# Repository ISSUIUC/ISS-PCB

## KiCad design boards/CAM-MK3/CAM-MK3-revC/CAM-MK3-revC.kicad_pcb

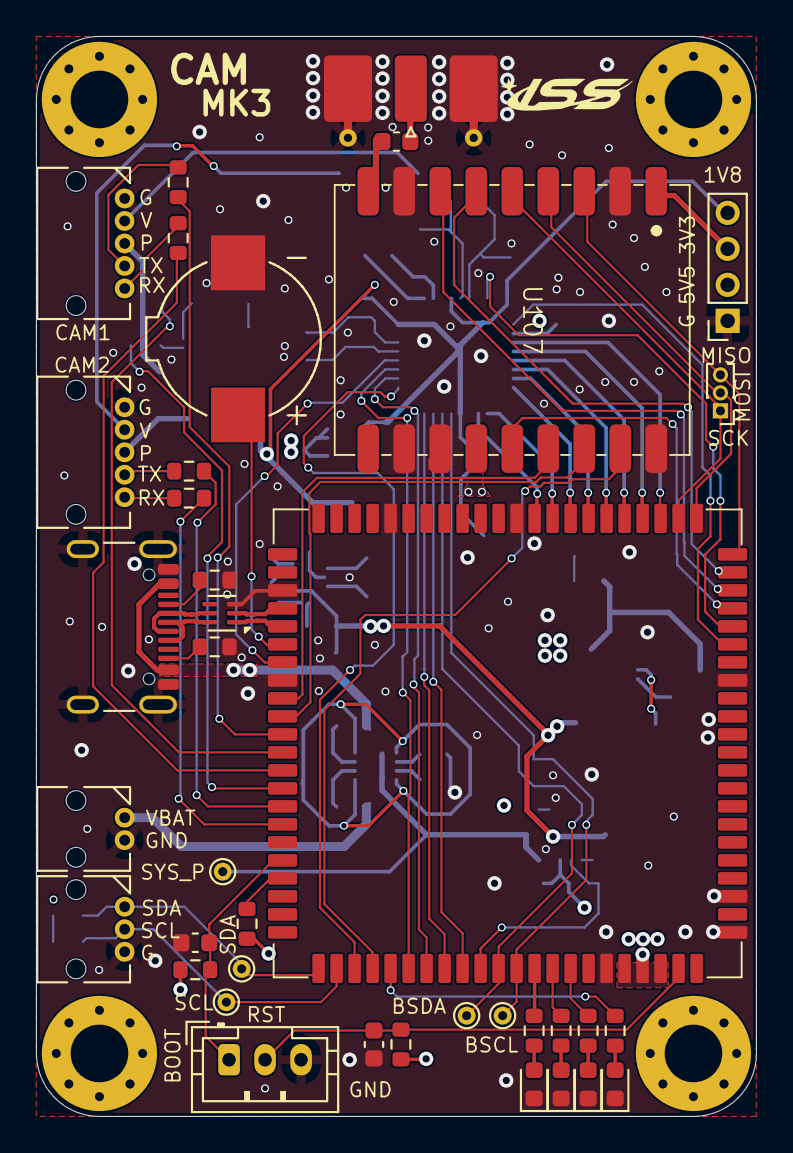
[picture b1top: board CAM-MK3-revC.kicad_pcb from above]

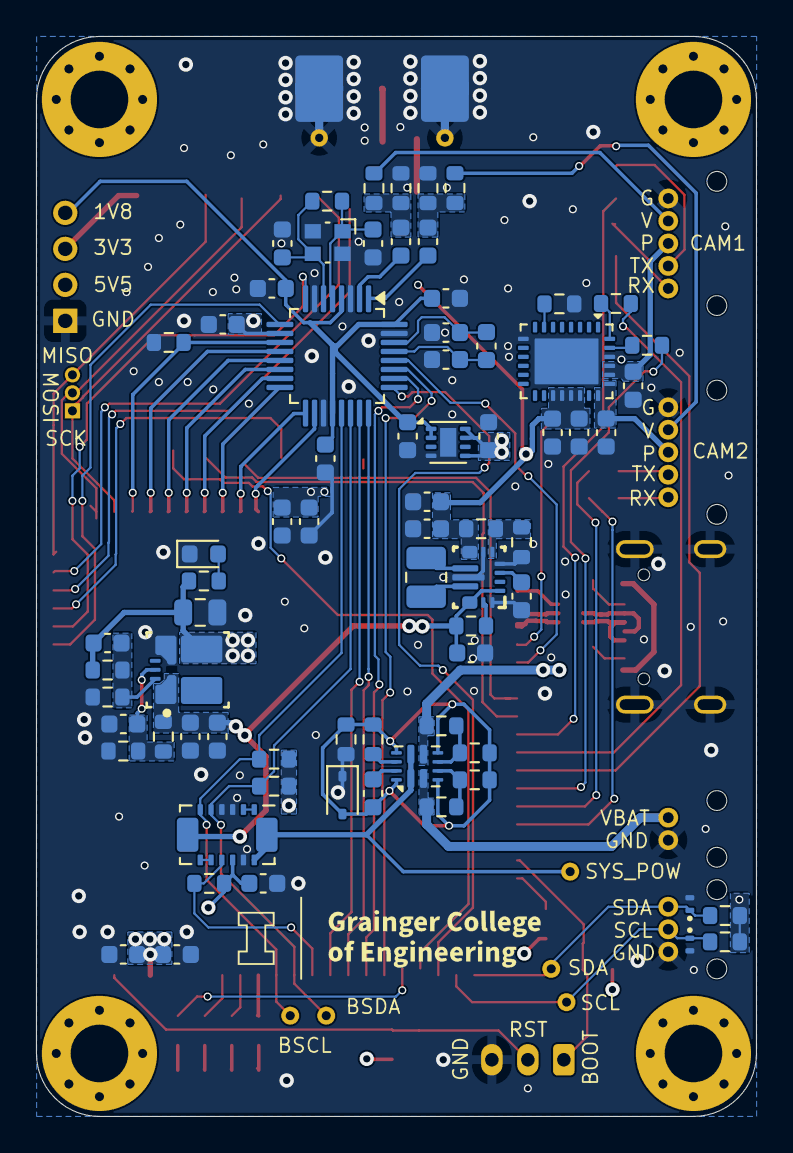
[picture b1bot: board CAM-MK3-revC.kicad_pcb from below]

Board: 4 copper layers, 40.0 x 60.0 mm, 115 parts (73 on the bottom side), 98 nets.

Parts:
BZ101: Buzzer; Buzzer_SMTB-0927-TW-R
C101, C106, C108, C109, C110, C111, C112, C114, C116, C117, C118, C121, C203, C204: 100nF; C_0603_1608Metric
C102, C103: 19pF; C_0603_1608Metric
C104, C105, C107, C115, C123, C210, C211, C212: 1uF; C_0603_1608Metric
C113: 22uF; C_0603_1608Metric
C119, C120: 22nF; C_0603_1608Metric
C122: 100pF; C_0603_1608Metric
C201, C202, C208: 10uF; C_0603_1608Metric
C205: 10nF; C_0603_1608Metric
C206: 22pF; C_0603_1608Metric
C207: 47uF; C_0603_1608Metric
C209: 33uF; C_0805_2012Metric
D101, D106: ESD321; Texas_DPY0002A_0.6x1mm_P0.65mm
D102, D202: RED LED; LED_0603_1608Metric
D103: ORANGE LED; LED_0603_1608Metric
D104: GREEN LED; LED_0603_1608Metric
D105: BLUE LED; LED_0603_1608Metric
D201: BAS416; D_SOD-323
H101, H102, H103, H104: MountingHole; MountingHole_3.2mm_M3_Pad_Via
J101: USB4105-GF-A; USB_C_Receptacle_GCT_USB4105-xx-A_16P_TopMnt_Horizontal
J102: 2200980271; Molex_Micro-Lock_2200980271_1x02_P1.25mm_Horizontal
J103: Conn_01x03; PinHeader_1x03_P1.00mm_Vertical
J104, J107: Conn_01x05; Molex_Micro-Lock_2200980571_1x05_P1.25mm_Horizontal
J105: Conn_01x03; Molex_Micro-Lock_2200980371_1x03_P1.25mm_Horizontal
J106: SMA; SMA_Molex_73251-2120_EdgeMount_Horizontal
J108: Conn_01x03; JST_PH_B3B-PH-K_1x03_P2.00mm_Vertical
J111: Conn_01x04; PinSocket_1x04_P2.00mm_Vertical
L201: 1.5uH; L_1008_2520Metric
R101, R102, R103, R104: 37.4; R_0603_1608Metric
R105, R210: 100k; R_0603_1608Metric
R106, R107: 10K; R_0603_1608Metric
R108, R109, R110, R120, R201, R203: 10k; R_0603_1608Metric
R111: 680; R_0603_1608Metric
R112, R113, R205, R207: 5.1k; R_0603_1608Metric
R114, R115: 4.7k; R_0603_1608Metric
R116, R117, R118, R119: 220; R_0603_1608Metric
R121, R122, R123, R124, R214: 470; R_0603_1608Metric
R125, R127: 2.2k; R_0603_1608Metric
R126: 20k; R_0603_1608Metric
R202: 22.1k; R_0603_1608Metric
R204: 19.6k; R_0603_1608Metric
R206: 39k; R_0603_1608Metric
R208: 0; R_0603_1608Metric
R209: 590k; R_0603_1608Metric
R211: 135k; R_0603_1608Metric
R212: 30k; R_0603_1608Metric
R213: 21.5k; R_0603_1608Metric
TP101, TP102, TP103, TP104, TP201: TestPoint; TestPoint_THTPad_D1.0mm_Drill0.5mm
U101: ESP32-P4-Module
U102: TVP5151; LQFP-32_5x5mm_P0.5mm
U104: ECMF02-2AMX6; ST_UQFN-6L_1.5x1.7mm_P0.5mm
U105: TPS274160B; WQFN-RLH0028A
U106: INA745x; VQFN-REL0014B
U107: LR2021
U201: TPS63070; VQFN-RNM0015A
U202: TPSM863252; QFN-FCMOD-RDX0007A
U203: TPS2121; Texas_VQFN-HR-12_2x2.5mm_P0.5mm
U204: TPS7A21-Q1; Texas_DSG0008A_WSON-8-1EP_2x2mm_P0.5mm_EP0.9x1.6mm
Y101: ABM10; Crystal_SMD_Abracon_ABM10-4Pin_2.5x2.0mm

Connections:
+1V8: C109.2, C112.2, C114.2, C212.1, J111.4, U102.4 (PLL_AVDD), U102.20 (DVDD), U102.32 (CH_AVDD), U204.1 (OUT), U204.2 (OUT)
+3V3: C108.1, C110.1, C113.1, C115.1, C116.1, C121.1, C206.1, C209.1, C211.1, J111.3, R106.2, R107.2, R114.1, R115.1, R120.1, R125.2, R126.2, R127.1, R211.1, R214.1, U101.84 (ESP_VBAT), U101.85 (ESP_3V3), U101.86 (ESP_3V3), U102.10 (IO_DVDD), U106.11 (VS), U107.1 (VCC), U202.3 (VOUT), U204.5 (EN), U204.7 (IN), U204.8 (IN)
+5V5: C117.1, C118.1, C207.1, C208.1, J111.2, R209.1, U105.17 (VS), U105.18 (VS), U105.19 (VS), U105.20 (VS), U201.7 (VOUT), U201.8 (VOUT)
/AVID: U101.73 (GPIO45), U102.26 (AVID/CLK_IN)
/BOARD_SCL: R115.2, TP103.1, U101.78 (GPIO50), U102.21 (SCL), U106.6 (SCL)
/BOARD_SDA: R114.2, TP104.1, U101.77 (GPIO49), U102.22 (SDA), U106.5 (SDA)
/BOOT_SW: C111.1, J108.1, R107.1, U101.62 (GPIO35)
/BUZZER: BZ101.1 (-), U101.50 (GPIO24)
/CAM_1_POW: C120.1, J104.3, U105.24 (OUT1), U105.25 (OUT1)
/CAM_2_POW: C119.1, J107.3, U105.22 (OUT2), U105.23 (OUT2)
/D+: J101.A6 (D+), J101.B6 (D+), U104.6 (D+_out)
/D-: J101.A7 (D-), J101.B7 (D-), U104.5 (D-_out)
/FID/GLCO: U101.75 (GPIO47), U102.23 (FID/GLCO)
/GPCL/VBLK: U101.72 (GPIO44), U102.27 (INTREQ/GPCL/VBLK)
/HSYNC: U101.69 (GPIO41), U102.25 (HSYNC)
/LED_BLUE: R124.1, U101.71 (GPIO43)
/LED_GREEN: R123.1, U101.81 (GPIO53)
/LED_ORANGE: R122.1, U101.80 (GPIO52)
/LED_RED: R121.1, U101.79 (GPIO51)
/LR2021_ANT: C122.2, U107.9 (ANT)
/LR2021_BUSY: U101.20 (GPIO5), U107.7 (BUSY)
/LR2021_CS: U101.21 (GPIO6), U107.6 (~CS)
/LR2021_GPIO7: U101.70 (GPIO42), U107.17 (DIO7)
/LR2021_GPIO8: U101.54 (GPIO27), U107.16 (DIO8)
/LR2021_GPIO9: U101.53 (GPIO26), U107.15 (DIO9)
/LR2021_nRST: U101.19 (GPIO4), U107.14 (nRST)
/ON_OFF_1: R109.1, U101.58 (GPIO31)
/ON_OFF_2: R110.1, U101.56 (GPIO29)
/PDN: U101.51 (GPIO25), U102.28 (PDN)
/Power/PMUX_GND: C210.1, D201.2 (A), R205.2, R207.2, R208.1, R213.1, U203.3 (CP2), U203.6 (PR1), U203.9 (ST), U203.12 (GND)
/RESET_SW: C123.1, J108.2, R126.1, U101.87 (CHIP_PU)
/RESET_VD: U101.18 (GPIO3), U102.8 (RESETB)
/RX_1: R116.2, U101.57 (GPIO30)
/RX_2: R118.2, U101.60 (GPIO33)
/SCL: D106.1 (K), J105.2, R127.2, TP101.1, U101.68 (GPIO40)
/SCLK: U101.17 (GPIO2), U102.9 (SCLK)
/SDA: D101.1 (K), J105.1, R125.1, TP102.1, U101.67 (GPIO39)
/SENSE_ALERT: R120.2, U101.76 (GPIO48), U106.10 (ALERT)
/SPI_MISO: J103.3, U101.22 (GPIO7), U107.3 (MISO)
/SPI_MOSI: J103.2, U101.23 (GPIO8), U107.4 (MOSI)
/SPI_SCK: J103.1, U101.24 (GPIO9), U107.5 (SCK)
/SYS_POWER: TP201.1, U106.13 (VBUS), U106.14 (IS+), U203.1 (OUT), U203.8 (OUT)
/TX_1: R117.2, U101.55 (GPIO28)
/TX_2: R119.2, U101.59 (GPIO32)
/USB_D+: U101.49 (DP), U104.1 (D+_in)
/USB_D-: U101.48 (DM), U104.2 (D-_in)
/USB_POWER: J101.A4 (VBUS), J101.A9 (VBUS), J101.B4 (VBUS), J101.B9 (VBUS), R204.1, U203.7 (IN1)
/VBAT: J102.1, R206.1, U203.2 (IN2)
/VIDEO_1: J104.2, R102.1
/VIDEO_2: J107.2, R104.1
/VREG_IN: C201.1, C202.1, C203.1, R201.1, R202.1, U106.7 (IS-), U201.1 (PS_SYNC), U201.12 (VIN), U201.13 (VIN), U202.1 (VIN)
/VSYNC: U101.74 (GPIO46), U102.24 (VSYNC/PALI)
/YOUT0: U101.32 (GPIO23), U102.18 (YOUT0)
/YOUT1: U101.31 (GPIO22), U102.17 (YOUT1)
/YOUT2: U101.30 (GPIO21), U102.16 (YOUT2)
/YOUT3: U101.29 (GPIO20), U102.15 (YOUT3)
/YOUT4: U101.28 (GPIO13), U102.14 (YOUT4)
/YOUT5: U101.27 (GPIO12), U102.13 (YOUT5)
/YOUT6: U101.26 (GPIO11), U102.12 (YOUT6)
/YOUT7: R108.2, U101.25 (GPIO10), U102.11 (YOUT7/I2CSEL)
GND: BZ101.2 (+), C102.1, C103.1, C104.1, C105.1, C108.2, C109.1, C110.2, C111.2, C112.1, C113.2, C114.1, C115.2, C116.2, C117.2, C118.2, C119.2, C120.2, C121.2, C123.2, C201.2, C202.2, C203.2, C204.2, C205.2, C207.2, C208.2, C209.2, C211.2, C212.2, D101.2 (A), D102.1 (K), D103.1 (K), D104.1 (K), D105.1 (K), D106.2 (A), D201.1 (K), D202.1 (K), J101.A1 (GND), J101.A12 (GND), J101.B1 (GND), J101.B12 (GND), J101.S1 (SHIELD), J102.2, J104.1, J105.3, J106.2 (Ext), J107.1, J108.3, J111.1, R101.1, R103.1, R108.1, R111.2, R112.1, R113.1, R203.2, R208.2, R210.2, R212.2, U101.1 (GND), U101.3 (GND), U101.15 (GND), U101.33 (GND), U101.40 (GND), U101.47 (GND), U101.52 (GND), U101.83 (GND), U102.3 (PLL_AGND), U102.7 (AGND), U102.19 (DGND), U102.31 (CH_AGND), U104.3 (GND), U105.9 (GND), U105.26 (GND), U105.29 (PowerPAD), U106.3 (A1), U106.4 (A0), U106.12 (GND), U107.2 (GND), U107.8 (GND), U107.11 (GND), U107.12 (GND), U107.18 (GND), U201.4 (GND), U201.6 (FB2), U201.10 (PGND), U201.15 (VSEL), U202.4 (PGND), U204.4 (GND), U204.9 (EPAD), Y101.2, Y101.4
unnamed: C101.1, R101.2, R102.2
unnamed: C106.1, R103.2, R104.2
unnamed: D102.2 (A), R121.2
unnamed: D103.2 (A), R122.2
unnamed: D104.2 (A), R123.2
unnamed: D105.2 (A), R124.2
unnamed: D202.2 (A), R214.2
unnamed: J101.A5 (CC1), R112.2
unnamed: J101.B5 (CC2), R113.2
unnamed: J104.4, R117.1
unnamed: J104.5, R116.1
unnamed: C122.1, J106.1 (In)
unnamed: J107.4, R119.1
unnamed: J107.5, R118.1
unnamed: R106.1, U101.63 (GPIO36)
unnamed: C106.2, U102.1 (AIP1A)
unnamed: C101.2, U102.2 (AIP1B)
unnamed: C105.2, C107.2, U102.30 (REFM)
unnamed: C104.2, C107.1, U102.29 (REFP)
unnamed: C103.2, R105.1, U102.5 (XTAL1/OSC), Y101.1
unnamed: C102.2, R105.2, U102.6 (XTAL2), Y101.3
unnamed: R111.1, U105.7 (CL)
unnamed: R109.2, U105.27 (EN1)
unnamed: R110.2, U105.28 (EN2)
unnamed: U106.1 (SH+), U106.2 (IN+)
unnamed: U106.8 (SH-), U106.9 (IN-)
unnamed: R201.2, U201.14 (EN)
unnamed: R209.2, R210.1, U201.5 (FB)
unnamed: L201.1, U201.11 (L1)
unnamed: L201.2, U201.9 (L2)
unnamed: C204.1, U201.3 (VAUX)
unnamed: C205.1, R202.2, R203.1, U202.6 (EN)
unnamed: C206.2, R211.2, R212.1, U202.7 (FB)
unnamed: R213.2, U203.10 (ILM)
unnamed: R204.2, R205.1, U203.5 (OV1)
unnamed: R206.2, R207.1, U203.4 (OV2)
unnamed: C210.2, U203.11 (SS)

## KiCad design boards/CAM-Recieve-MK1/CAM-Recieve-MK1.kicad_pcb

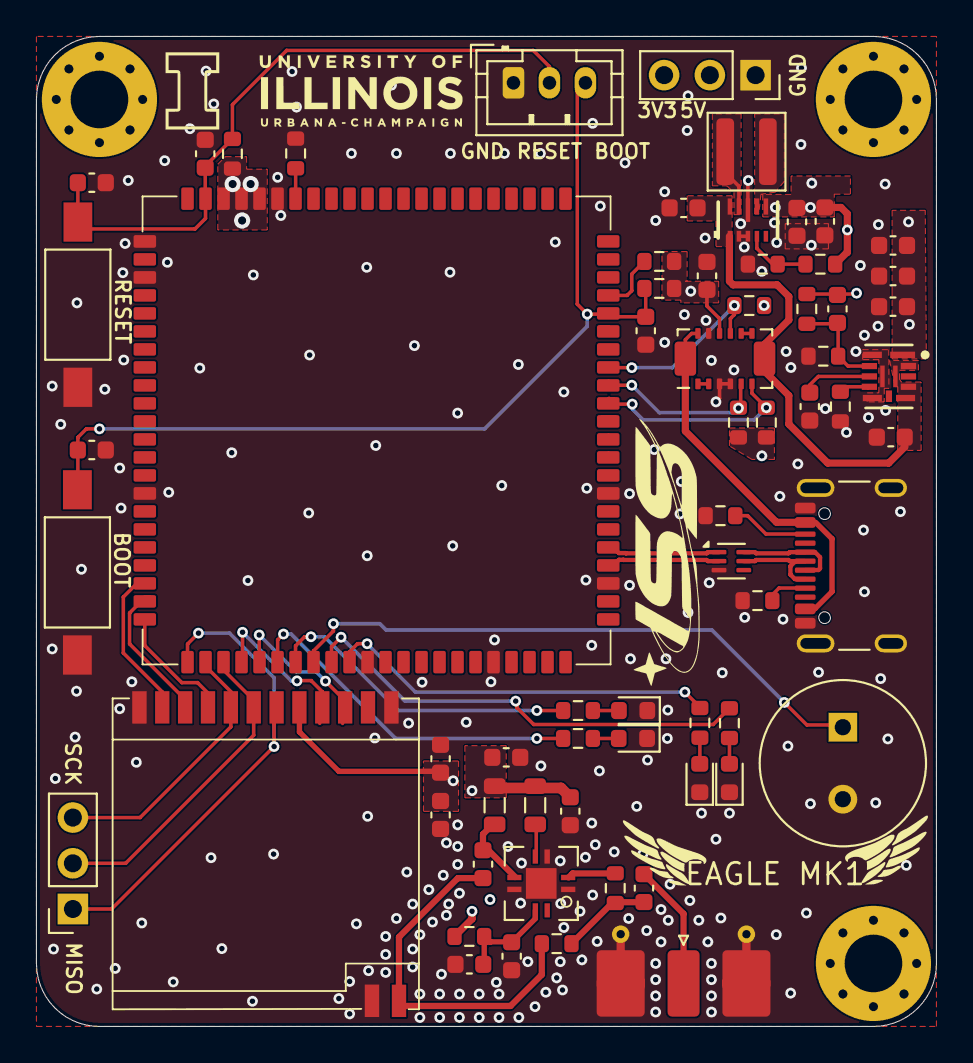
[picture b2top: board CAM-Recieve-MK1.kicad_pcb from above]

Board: 4 copper layers, 50.0 x 55.0 mm, 68 parts (0 on the bottom side), 50 nets.

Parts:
BZ101: Buzzer; MagneticBuzzer_PUI_AT-0927-TT-6-R
C1, C2, C4, C5, C6, C45, C48: 22uF; C_0603_1608Metric
C3, C7, C8: .1uF; C_0603_1608Metric
C10, C34, C36, C120: 1uF; C_0603_1608Metric
C31: 100nF; C_0603_1608Metric
C33, C35, C37, C49: 100pF; C_0603_1608Metric
C46: 4.7nF; C_0603_1608Metric
C47: 10pF; C_0603_1608Metric
C114: 0.1uF; C_0603_1608Metric
D104: RED LED; LED_0603_1608Metric
D105: ORANGE LED; LED_0603_1608Metric
D106: GREEN LED; LED_0603_1608Metric
D107: BLUE LED; LED_0603_1608Metric
H101, H103, H104: MountingHole; MountingHole_3.2mm_M3_Pad_Via
J1: SMA; SMA_Molex_73251-2120_EdgeMount_Horizontal
J101: USB4105-GF-A; USB_C_Receptacle_GCT_USB4105-xx-A_16P_TopMnt_Horizontal
J107: Conn_01x03; JST_PH_B3B-PH-K_1x03_P2.00mm_Vertical
J108, J109: Conn_01x03; PinSocket_1x03_P2.54mm_Vertical
L1: 36nH; L_0805_2012Metric
L2: 47nH; L_0805_2012Metric
L4: 470nH; L_Wuerth_MAPI-4030
R1: 806K; R_0603_1608Metric
R2: 91K; R_0603_1608Metric
R3, R4, R118, R119: 0; R_0603_1608Metric
R5, R14, R19: 10K; R_0603_1608Metric
R16: 100K; R_0603_1608Metric
R18: 453K; R_0603_1608Metric
R105, R106: 5.1k; R_0603_1608Metric
R116: 10k; R_0603_1608Metric
R117, R122: 4.7k; R_0603_1608Metric
R140: 20k; R_0603_1608Metric
R141, R142, R143, R144: 470; R_0603_1608Metric
SW2, SW3: SW_Push; SW_SPST_FSMSM
U1: RF4463PRO
U2: TPS63802; DLA0010A
U4: PMA-545G1+; QFN-8-1EP_3x3mm_P1.2mm_EP1.7x1.7mm
U5: TPSM82813SILR; QFN-FCMOD-VCA0013A
U7: ESP32-P4-Module-Waveshare
U101: ECMF02-2AMX6; ST_UQFN-6L_1.5x1.7mm_P0.5mm
U106: INA745x; VQFN-REL0014B

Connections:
+3V3: C4.2, C5.2, C10.1, C31.1, C47.2, C48.2, C114.1, J108.3, R5.2, R18.2, R19.2, R116.1, R117.1, R122.1, R140.2, U1.5 (VCC), U5.1 (VOUT), U7.84 (ESP_VBAT), U7.85 (ESP_3V3), U7.86 (ESP_3V3), U106.11 (VS)
+5V: C2.2, C6.2, C35.2, C36.2, J108.2, L1.2, L2.2, R1.1, R4.2, U2.6 (VOUT)
/Antenna_Connector: C49.2, R118.2, R119.2
/Antenna_Connector_T: R118.1, U4.2 (RFIN)
/BOOT_SW: C3.1, C8.1, J107.3, R5.1, SW3.1, U7.62 (GPIO35)
/BUZZER: BZ101.1 (-), U7.30 (GPIO21)
/D+: J101.A6 (D+), J101.B6 (D+), U101.6 (D+_out)
/D-: J101.A7 (D-), J101.B7 (D-), U101.5 (D-_out)
/LED_BLUE: R144.1, U7.29 (GPIO20)
/LED_GREEN: R143.1, U7.28 (GPIO13)
/LED_ORANGE: R142.1, U7.31 (GPIO22)
/LED_RED: R141.1, U7.32 (GPIO23)
/RESET_SW: C7.1, C120.1, J107.2, R140.1, SW2.1, U7.87 (CHIP_PU)
/SENSE_ALERT: R116.2, U7.59 (GPIO32), U106.10 (ALERT)
/SENSE_SCL: R122.2, U7.57 (GPIO30), U106.6 (SCL)
/SENSE_SDA: R117.2, U7.58 (GPIO31), U106.5 (SDA)
/SPI_MISO: J109.1, U1.6 (SD0), U7.23 (GPIO8)
/SPI_MOSI: J109.2, U1.7 (SDI), U7.25 (GPIO10)
/SPI_SCK: J109.3, U1.8 (SCLK), U7.24 (GPIO9)
/SYS_POWER: J101.A4 (VBUS), J101.A9 (VBUS), J101.B4 (VBUS), J101.B9 (VBUS), U106.13 (VBUS), U106.14 (IS+)
/Si4463_ANT: C37.1, R119.1, U1.14 (ANT)
/Si4463_CS: U1.9 (nSEL), U7.22 (GPIO7)
/Si4463_EN: U1.11 (SDN), U7.20 (GPIO5)
/Si4463_GPIO0: U1.3 (GPIO0), U7.27 (GPIO12)
/Si4463_GPIO1: U1.4 (GPIO1), U7.26 (GPIO11)
/Si4463_nIRQ: U1.10 (nIRQ), U7.21 (GPIO6)
/USB_D+: U7.49 (DP), U101.1 (D+_in)
/USB_D-: U7.48 (DM), U101.2 (D-_in)
/VREG_IN: C1.2, C45.2, U2.1 (EN), U2.10 (VIN), U5.8 (VIN), U5.9 (EN), U5.11 (MODE_SYNC), U5.13 (VIN), U106.7 (IS-)
GND: BZ101.2 (+), C1.1, C2.1, C3.2, C4.1, C5.1, C6.1, C7.2, C8.2, C10.2, C31.2, C33.2, C34.2, C35.1, C36.1, C45.1, C46.1, C48.1, C114.2, C120.2, D104.1 (K), D105.1 (K), D106.1 (K), D107.1 (K), J1.2 (Ext), J101.A1 (GND), J101.A12 (GND), J101.B1 (GND), J101.B12 (GND), J101.S1 (SHIELD), J107.1, J108.1, R2.2, R3.2, R14.2, R16.1, R105.1, R106.1, SW2.2, SW3.2, U1.1 (GND), U1.12 (GND), U1.13 (GND), U2.2 (MODE), U2.3 (AGND), U2.8 (GND), U4.1 (NC), U4.3 (NC), U4.6 (NC), U4.9 (GND), U5.2 (GND), U5.6 (GND), U5.12 (GND), U7.1 (GND), U7.3 (GND), U7.15 (GND), U7.33 (GND), U7.40 (GND), U7.47 (GND), U7.52 (GND), U7.83 (GND), U101.3 (GND), U106.3 (A1), U106.4 (A0), U106.12 (GND)
unnamed: C33.1, C34.1, R4.1, U4.7 (BIAS)
unnamed: D104.2 (A), R141.2
unnamed: D105.2 (A), R142.2
unnamed: D106.2 (A), R143.2
unnamed: D107.2 (A), R144.2
unnamed: C49.1, J1.1 (In)
unnamed: J101.A5 (CC1), R105.2
unnamed: J101.B5 (CC2), R106.2
unnamed: L1.1, U4.4 (BIAS)
unnamed: R1.2, R2.1, U2.4 (FB)
unnamed: L4.1, U2.9 (L1)
unnamed: L4.2, U2.7 (L2)
unnamed: C37.2, L2.1, U4.5 (RFOUT)
unnamed: R14.1, U5.5 (COMP_FSET)
unnamed: C47.1, R16.2, R18.1, U5.3 (FB)
unnamed: C46.2, U5.4 (SS_TR)
unnamed: R19.1, U7.63 (GPIO36)
unnamed: R3.1, U7.82 (GPIO54)
unnamed: U106.1 (SH+), U106.2 (IN+)
unnamed: U106.8 (SH-), U106.9 (IN-)

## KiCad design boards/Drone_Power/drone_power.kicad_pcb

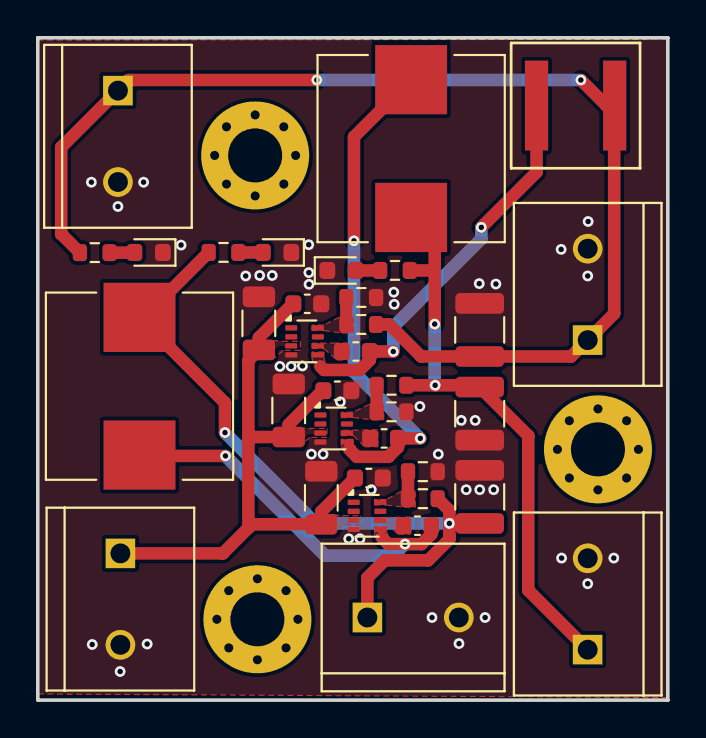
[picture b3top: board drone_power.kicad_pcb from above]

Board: 2 copper layers, 35.0 x 36.8 mm, 38 parts (0 on the bottom side), 17 nets.

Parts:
C1, C3, C6, C7, C10, C11: 100nF; C_0603_1608Metric
C2, C5, C9: 10uF; C_1206_3216Metric
C4, C8, C12: 47uF; C_1210_3225Metric
D1: BLUE LED; LED_0603_1608Metric
D2: GREEN LED; LED_0603_1608Metric
D3: RED LED; LED_0603_1608Metric
H1, H2, H3: MountingHole_Pad; MountingHole_3mm_Pad_Via
J1, J2, J3, J4, J5: Screw_Terminal_01x02; TE_282837-2
L1, L2: 7.8uH; L_Wuerth_HCI-1050
L3: 12uH; IND_XGL6060_COC
R1, R3: 52.3k; R_0603_1608Metric
R2, R4, R6: 10k; R_0603_1608Metric
R5: 140k; R_0603_1608Metric
R7, R8: 140; R_0603_1608Metric
R9: 500; R_0603_1608Metric
U1, U2, U3: TPS563300; SOT-583-8

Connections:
unnamed: D1.2 (A), R7.2
unnamed: C1.2, C2.2, C4.2, C5.2, C6.2, C8.2, C9.2, C10.2, C12.2, D1.1 (K), D2.1 (K), D3.1 (K), J1.2, J2.2, J3.2, J4.2, J5.2, R2.2, R4.2, R6.2, U1.4 (GND), U2.4 (GND), U3.4 (GND)
unnamed: D2.2 (A), R8.2
unnamed: D3.2 (A), R9.2
unnamed: C12.1, J1.1, J4.1, L3.2, R5.1, R9.1
unnamed: C4.1, J2.1, L1.2, R1.1, R8.1
unnamed: C8.1, J3.1, L2.2, R3.1, R7.1
unnamed: C1.1, C2.1, C5.1, C6.1, C9.1, C10.1, J5.1, U1.3 (VIN), U2.3 (VIN), U3.3 (VIN)
unnamed: C3.1, U1.6 (BST)
unnamed: R1.2, R2.1, U1.8 (FB)
unnamed: C3.2, L1.1, U1.5 (SW)
unnamed: C7.1, U2.6 (BST)
unnamed: R3.2, R4.1, U2.8 (FB)
unnamed: C7.2, L2.1, U2.5 (SW)
unnamed: C11.1, U3.6 (BST)
unnamed: R5.2, R6.1, U3.8 (FB)
unnamed: C11.2, L3.1, U3.5 (SW)

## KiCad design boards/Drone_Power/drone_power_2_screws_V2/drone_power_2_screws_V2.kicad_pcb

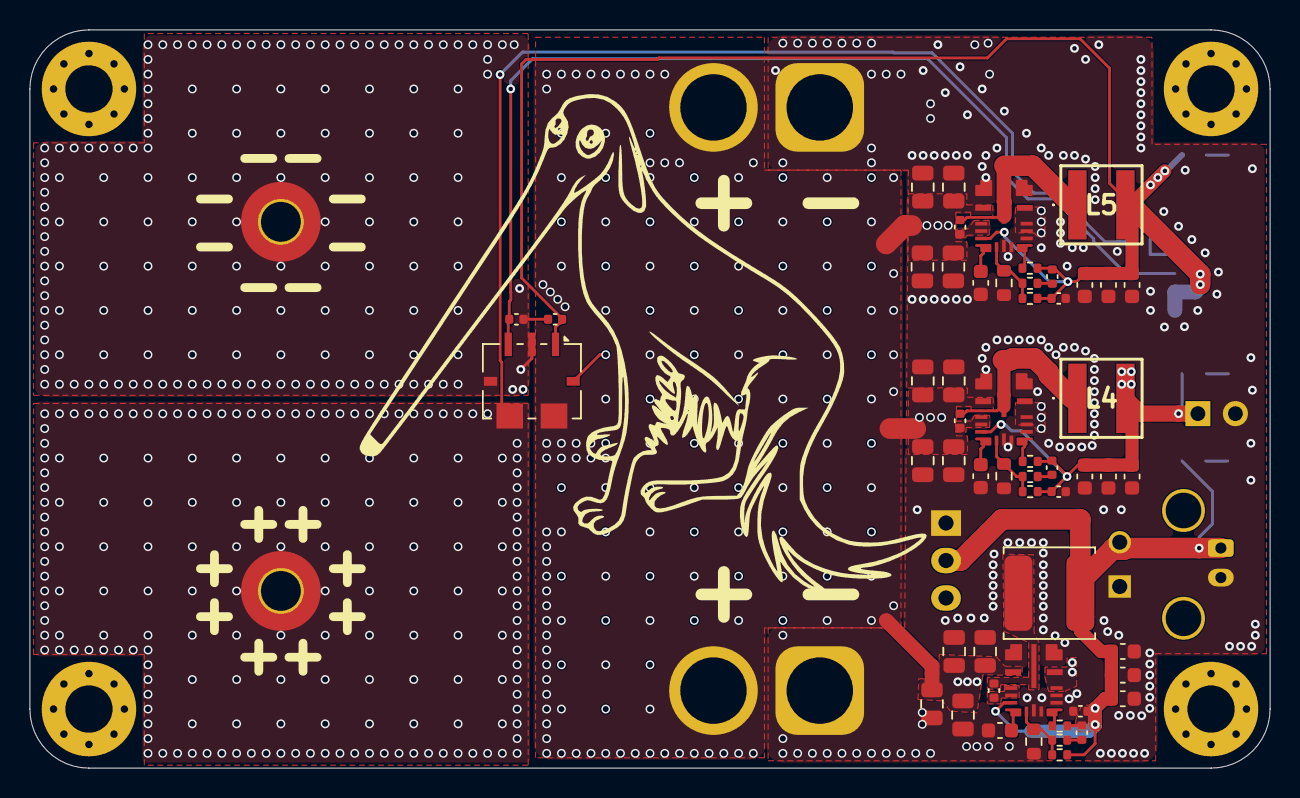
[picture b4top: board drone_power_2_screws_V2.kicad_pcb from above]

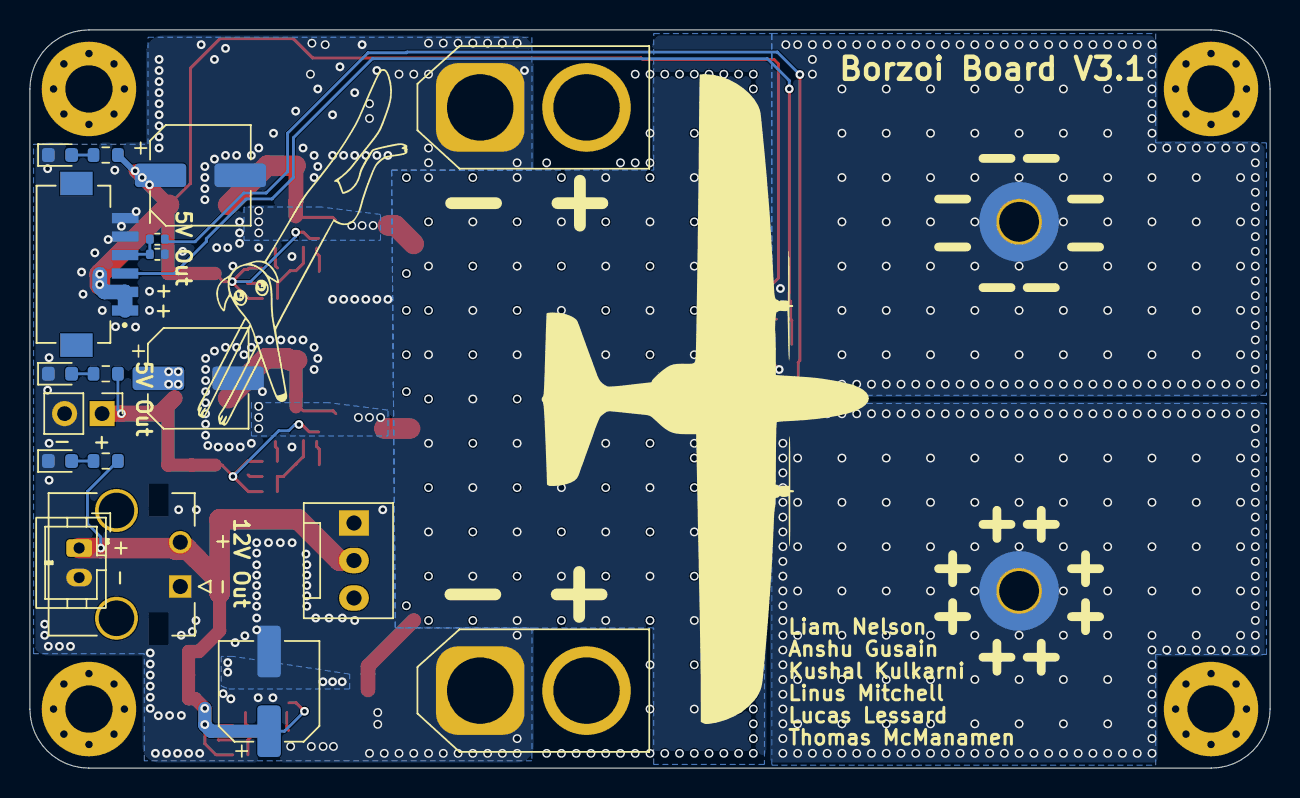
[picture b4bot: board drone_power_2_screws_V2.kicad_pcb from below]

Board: 6 copper layers, 84.0 x 50.0 mm, 78 parts (18 on the bottom side), 29 nets.

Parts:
C1: .1uF; C_0402_1005Metric
C2: 1nF; C_0402_1005Metric
Cbias1, Cbias2, Cbias3: 100nF; C_0402_1005Metric
Cboot2, Cboot4, Cboot5: 100nF; C_0402_1005Metric
Cff2, Cff4, Cff5: 15pF; C_0402_1005Metric
Cin_1, Cin_2, Cin_3, Cin_4, Cin_5, Cin_6: 10uF; C_0805_2012Metric
Cin_x1, Cin_x2, Cin_x3, Cin_x4, Cin_x5, Cin_x6: 1uF; C_0805_2012Metric
Cout2, Cout3, Cout4, Cout5, Cout6, Cout7, Cout8, Cout9, Cout10: 22uF; C_0603_1608Metric
Cout11, Cout12, Cout13: 220uF; CP_Elec_6.3x7.7
Cvcc1, Cvcc2, Cvcc3: 1uF; C_0603_1608Metric
D1: RED LED; LED_0603_1608Metric
D2: GREEN LED; LED_0603_1608Metric
D3: BLUE LED; LED_0603_1608Metric
H1, H2, H3, H4: MountingHole_Pad; MountingHole_3.2mm_M3_Pad_Via
H5: MountingHole_Pad; MountingHole_2.7mm_Pad_TopBottom
H6: MountingHole_Pad; MountingHole_2.7mm_M2.5_Pad_TopBottom
IC1: ACS72981LLRATR-100B5; Allegro_PSOF-7_4.8x6.4mm_P1.60mm
J1: Conn_01x02_Pin; JST_PH_B2B-PH-K_1x02_P2.00mm_Vertical
J2, J4: Conn_01x02_Pin; AMASS_XT60-M_1x02_P7.20mm_Vertical
J3: Conn_01x02_Pin; Molex_Micro-Fit-Plus_0436500203_1x02_P3.0mm
J5: Conn_01x02_Pin; PinHeader_1x02_P2.54mm_Vertical
J6: Conn_01x06_Pin; HRS_DF13A-6P-1.25H_51_
L3: 2.2uH; L_TDK_VLS6045EX_VLS6045AF
L4, L5: 1.4uH; MPS_MPLAL50301R5
M1: Fan_3pin; FanPinHeader_1x03_P2.54mm_Vertical
R1, R2: 3.3k; R_0603_1608Metric
R3: 4.7k; R_0603_1608Metric
R6: 100k; R_0402_1005Metric
R7: 22k; R_0402_1005Metric
Rfbb2: 9.09k Ohms; R_0603_1608Metric
Rfbb4, Rfbb5: 24.9k Ohms; R_0603_1608Metric
Rfbt2, Rfbt4, Rfbt5: 100k Ohm; R_0402_1005Metric
Rff2, Rff4, Rff5: 4.99k Ohms; R_0402_1005Metric
Rreset1, Rreset2, Rreset3: 100k Ohm; R_0402_1005Metric
U3, U4, U5: LM62460; VQFN-HR-RPH0016B

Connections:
/5V_NAVIO: C1.1, Cbias3.1, Cff5.1, Cout5.2, Cout9.2, Cout10.2, Cout11.1, IC1.1 (VCC), J6.1, J6.2, L5.2, R1.1, Rfbt5.2, Rreset3.2, U5.5 (BIAS)
/5V_SERVO: Cbias2.1, Cff4.1, Cout4.2, Cout7.2, Cout8.2, Cout12.1, J5.1, L4.2, R2.1, Rfbt4.2, Rreset2.2, U4.5 (BIAS)
/12V: Cbias1.1, Cff2.1, Cout2.2, Cout3.2, Cout6.2, Cout13.1, J1.1, J3.2, L3.2, M1.2 (+), R3.1, Rfbt2.2, Rreset1.2, U3.5 (BIAS)
/G_Batt: C1.2, C2.2, Cbias1.2, Cbias2.2, Cbias3.2, Cin_1.2, Cin_2.2, Cin_3.2, Cin_4.2, Cin_5.2, Cin_6.2, Cin_x1.2, Cin_x2.2, Cin_x3.2, Cin_x4.2, Cin_x5.2, Cin_x6.2, Cout2.1, Cout3.1, Cout4.1, Cout5.1, Cout6.1, Cout7.1, Cout8.1, Cout9.1, Cout10.1, Cout11.2, Cout12.2, Cout13.2, Cvcc1.2, Cvcc2.2, Cvcc3.2, D1.1 (K), D2.1 (K), D3.1 (K), H6.1 (1_1), IC1.2 (GND), IC1.4 (NC_1), IC1.7 (NC_2), J1.2, J2.1, J3.1, J4.1, J5.2, J6.5, J6.6, M1.1 (-), R7.2, Rfbb2.1, Rfbb4.1, Rfbb5.1, U3.1 (PGND), U3.8 (AGND), U3.9 (RT), U3.11 (SPSP), U3.12 (SYNC/MODE), U3.15 (PGND), U4.1 (PGND), U4.8 (AGND), U4.9 (RT), U4.11 (SPSP), U4.12 (SYNC/MODE), U4.15 (PGND), U5.1 (PGND), U5.8 (AGND), U5.9 (RT), U5.11 (SPSP), U5.12 (SYNC/MODE), U5.15 (PGND)
/IP-: Cin_1.1, Cin_2.1, Cin_3.1, Cin_4.1, Cin_5.1, Cin_6.1, Cin_x1.1, Cin_x2.1, Cin_x3.1, Cin_x4.1, Cin_x5.1, Cin_x6.1, IC1.6 (IP-), J2.2, J4.2, U3.2 (VIN), U3.13 (EN), U3.14 (VIN), U4.2 (VIN), U4.13 (EN), U4.14 (VIN), U5.2 (VIN), U5.13 (EN), U5.14 (VIN)
/I_SENSE: C2.1, IC1.3 (VIOUT), J6.3
/P_Batt: H5.1 (1_1), IC1.5 (IP+), R6.1
/V_SENSE: J6.4, R6.2, R7.1
unnamed: Cff2.2, Rff2.1
unnamed: Cff4.2, Rff4.1
unnamed: Cff5.2, Rff5.1
unnamed: D1.2 (A), R1.2
unnamed: D2.2 (A), R2.2
unnamed: D3.2 (A), R3.2
unnamed: Cboot2.2, U3.3 (RBOOT), U3.4 (CBOOT)
unnamed: Rfbb2.2, Rfbt2.1, Rff2.2, U3.7 (FB)
unnamed: Cboot2.1, L3.1, U3.16 (SW)
unnamed: Cvcc1.1, U3.6 (VCC)
unnamed: Rreset1.1, U3.10 (~RESET)
unnamed: Cboot4.2, U4.3 (RBOOT), U4.4 (CBOOT)
unnamed: Rfbb4.2, Rfbt4.1, Rff4.2, U4.7 (FB)
unnamed: Cboot4.1, L4.1, U4.16 (SW)
unnamed: Cvcc2.1, U4.6 (VCC)
unnamed: Rreset2.1, U4.10 (~RESET)
unnamed: Cboot5.2, U5.3 (RBOOT), U5.4 (CBOOT)
unnamed: Rfbb5.2, Rfbt5.1, Rff5.2, U5.7 (FB)
unnamed: Cboot5.1, L5.1, U5.16 (SW)
unnamed: Cvcc3.1, U5.6 (VCC)
unnamed: Rreset3.1, U5.10 (~RESET)
